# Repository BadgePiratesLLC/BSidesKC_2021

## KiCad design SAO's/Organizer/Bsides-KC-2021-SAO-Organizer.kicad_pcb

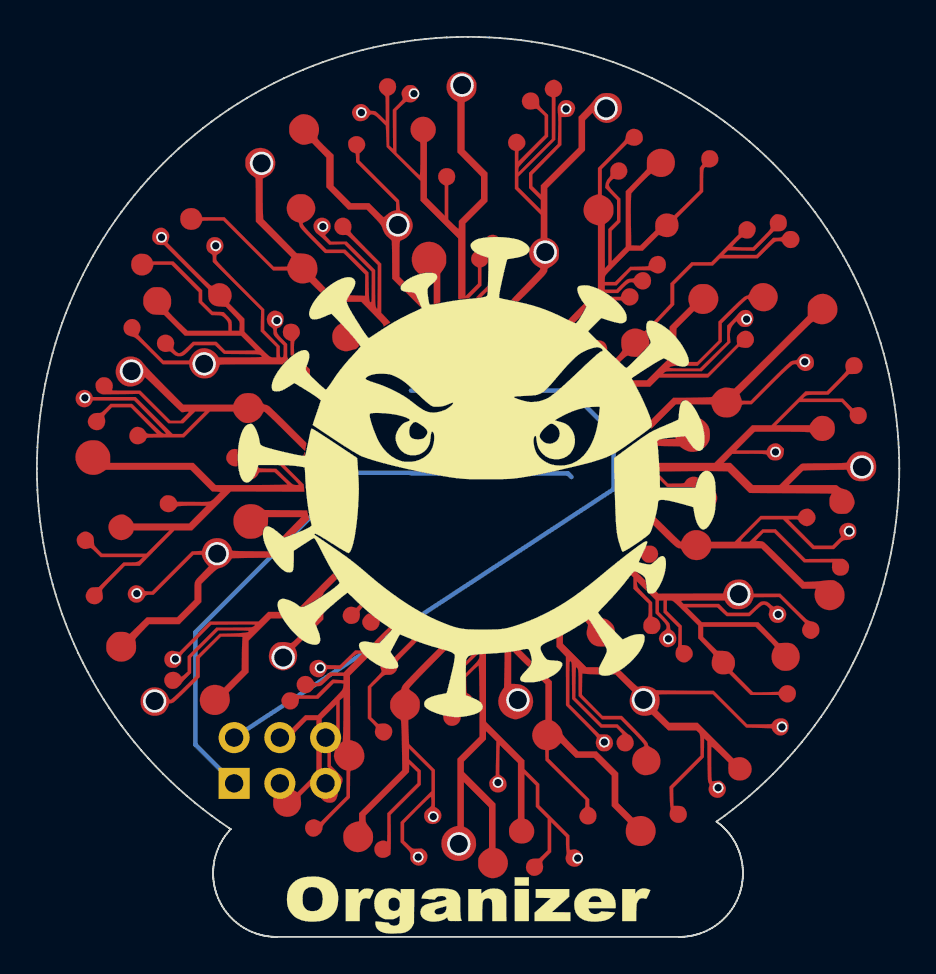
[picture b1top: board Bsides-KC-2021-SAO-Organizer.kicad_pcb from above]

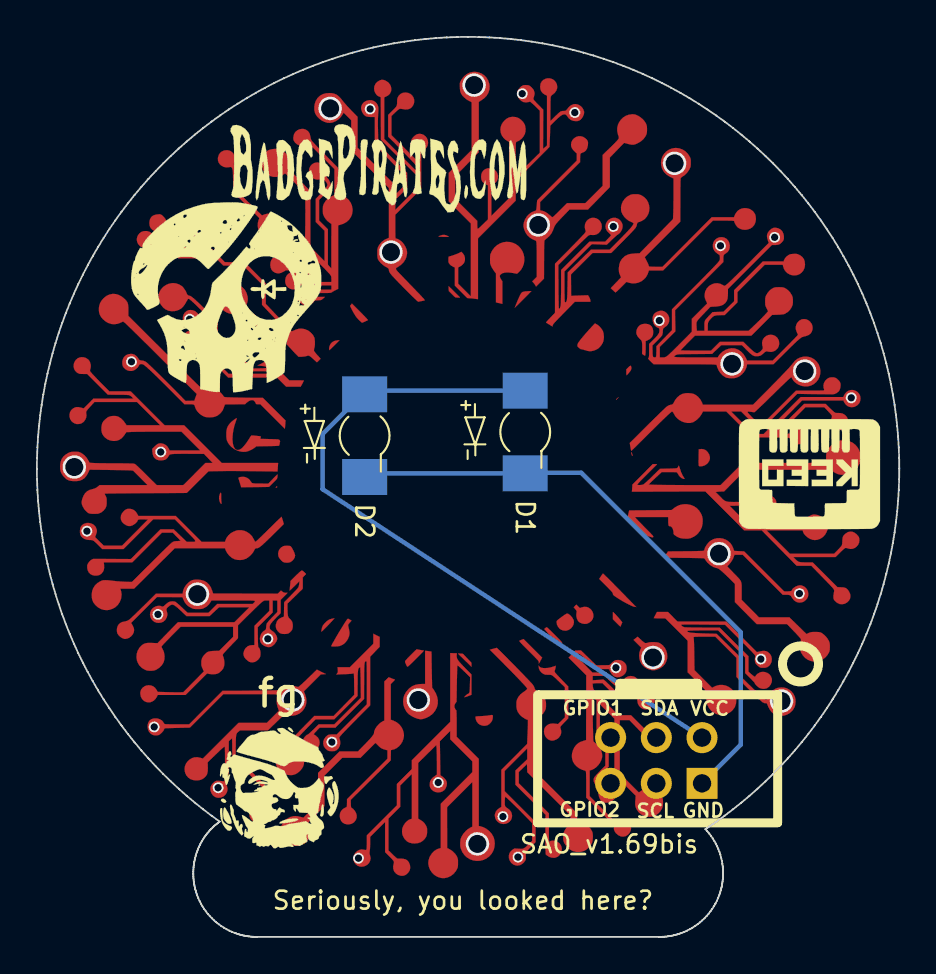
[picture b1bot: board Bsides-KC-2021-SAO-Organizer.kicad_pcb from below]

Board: 2 copper layers, 47.9 x 50.0 mm, 3 parts (2 on the bottom side), 2 nets.

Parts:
D1, D2: LED; LED_Osram_Lx_P47F_D2mm_ReverseMount_MaskNoHole
X1: SAO_v1.69bis; Badgelife-SAOv169-BADGE-2x3_Back

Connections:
GND: D1.1, D2.1, X1.2
VCC: D1.2, D2.2, X1.1
